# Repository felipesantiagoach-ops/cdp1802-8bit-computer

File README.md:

# CDP1802 8-bit Computer — Design and Construction

Design, construction and testing of an 8-bit microcomputer built around the **RCA CDP1802**, the first CMOS microprocessor (also known for flying in the Galileo probe and the Hubble Space Telescope).

Final engineering project for *Proyecto y Diseño Electrónico* (ET546), Electronic Engineering, **Universidad Nacional de Misiones**, Argentina (November 2022).

📄 **[Read the full report (PDF, Spanish)](informe/ProyectoFinal.pdf)**: 166 pages covering theory, schematics, PCBs, assembly code and test results.  
🖼️ **[Project poster](Poster_PyD_2022_Grupo_A.pdf)**

---

## Overview

The project was developed in three stages of increasing complexity. Each stage was designed in KiCad, simulated, and (for the first two) built and tested on hardware.

| Stage | Status | Highlights |
|---|---|---|
| **Minimal system** | ✅ Built and tested | CDP1802 + 8K EEPROM, 8-bit addressing, jumper-selectable program banks, single-sided PCB |
| **Medium system** | ✅ Built and tested | 16-bit addressing (64 KB), 32K EEPROM + 32K RAM, USB-UART link, runs Tiny BASIC and a diskless Elf/OS |
| **Final system** | 📐 Designed (schematics + PCB) | Power supply, bank-switched memory, I²C and SPI serial memories, 12-bit ADC, parallel I/O |

### 1. Minimal system
- CDP1802 with an AT28C64 EEPROM using only the 8 low address lines (256-byte programs).
- A8/A9 set by jumpers, allowing four independent programs in the same EEPROM without reprogramming.
- Four assembly programs written and verified on hardware: LED blink, push-button input, conditional blink, and a **bit-banged UART transmitter at 600 baud** using the Q output, with the delay loop derived analytically from the instruction cycle timing.
- Subroutines use the CDP1802 *SEP technique*, which requires no RAM (the system has none).

### 2. Medium system
- 74HC373 address latch to demultiplex the CDP1802's time-shared address bus to a full **16-bit / 64 KB** space.
- Memory map: 32K EEPROM (program) + 32K DS1744 timekeeping RAM (data).
- FT232RL USB-UART module for communication with a PC terminal (Tera Term).
- Ported and ran third-party software on real hardware:
  - **Tiny BASIC interpreter**: modified the source (register definitions, idle line polarity, autorun) and reassembled it.
  - **Diskless Elf/OS** operating system.

### 3. Final system (design)
Fully backwards compatible with the previous stages. Designed as a modular set of schematics and a double-sided 30 × 30 cm PCB:
- **Linear power supply** with line filter and ±12 V / 5 V regulation.
- **Bank-switched memory map**: boot mode (EEPROM + RAM) and run mode (program copied to RAM, a second RAM swapped in to maximise working memory).
- **Hardware SPI engine** built from discrete logic (MC14014 + 74HC595 shift registers, 74HC161/74HC74/74HC73 clock generator producing exactly 8 pulses at 2 MHz), which offloads the serial shifting from the CPU. Intended for a **microSD** card.
- **I²C serial memories**: 24LC1025 EEPROM and MB85RC64A **FRAM**, driven in software through the parallel port.
- **12-bit ADC** (MAX127) with OPA4277 signal conditioning for **4–20 mA** industrial current loops.
- **82C55 parallel I/O** mapped into the CDP1802's dedicated I/O space (INP/OUT instructions).

The report also outlines future work, including I/O drivers, SD-card support, a PLC-oriented use case and guidelines for a real-time operating system.

---

## Tools

| Area | Tools |
|---|---|
| Schematics and PCB | KiCad |
| Assembly and simulation | A18 cross-assembler, Emma02 emulator (debugging and instruction tracing) |
| Programming hardware | XGecu TL866 universal programmer; an Arduino-based EEPROM programmer was also built |
| Communication | FT232RL, Tera Term |
| Documentation | LaTeX (memoir, biblatex/biber), Git, VS Code |

---

## Repository structure

```
Poster_PyD_2022_Grupo_A.pdf   Project poster
informe/
  ProyectoFinal.pdf           Compiled report (Spanish)
  Codigo fuente/              LaTeX source (chapters, appendices, bibliography, figures)
archivos_de_kicad/            KiCad projects: schematics, PCBs, BOMs and exports
  1_Sistema_minimo/
  2_Sistema_medio/
  3_Sistema_final/            Full system plus separate sub-projects (ADC conditioning, SPI)
programas/                    CDP1802 assembly programs (.asm), assembled output (.hex, .lst) and build scripts
decodificador SPI/            Proteus simulations of the hardware SPI circuit
```

The KiCad projects were made with KiCad 6 (the minimal system also includes the original KiCad 5 files).  
Programs are assembled with the [A18 cross-assembler](https://www.retrotechnology.com/memship/a18.html); each folder includes a `.bat` script that assembles the `.asm` file with the same name.

### Building the report
Requires a LaTeX distribution (MiKTeX or TeX Live) with `biber`.

```bash
cd "informe/Codigo fuente"
pdflatex proyecto
biber proyecto
pdflatex proyecto
pdflatex proyecto
```

---

## Third-party software

The `programas/` folder also contains third-party code that was studied, modified or run on the hardware. It is included for reference, and credit goes to its original authors:
- **Tiny BASIC** for the 1802, from the [Membership Card](http://www.sunrise-ev.com/1802.htm) project (the `original/` folder is unmodified; `modificado/` contains our changes).
- **FIG-Forth** for the 1802, from Lee Hart's Membership Card resources.

---

## Authors

- **Felipe Santiago Alegre Chamorro**
- Atilio Boher
- Uriel Adrián Vera

Supervisor: Ing. Ricardo A. Korpys, Facultad de Ingeniería, UNaM.

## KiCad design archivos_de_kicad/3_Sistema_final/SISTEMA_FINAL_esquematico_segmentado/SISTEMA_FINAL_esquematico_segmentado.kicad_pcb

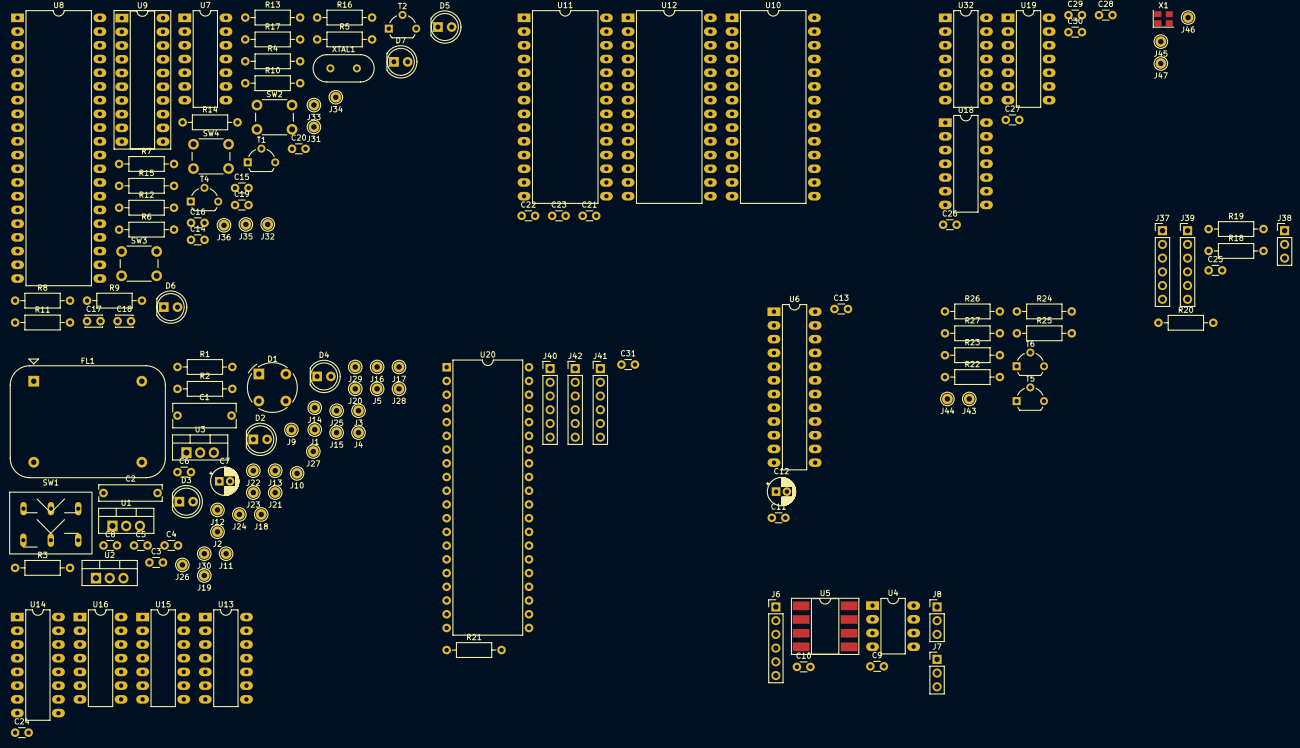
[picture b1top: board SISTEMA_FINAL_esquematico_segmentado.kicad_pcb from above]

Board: 2 copper layers, 144 parts (0 on the bottom side), 133 nets, no tracks yet.

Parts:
C1: 4700 uf; C_Rect_L11.5mm_W4.3mm_P10.00mm_MKT
C2: 4700 uf; C_Rect_L11.5mm_W2.8mm_P10.00mm_MKT
C3, C4: 0.33; C_Disc_D3.0mm_W1.6mm_P2.50mm
C5, C8: 0.1uf; C_Disc_D3.0mm_W1.6mm_P2.50mm
C6: 0.1 uf; C_Disc_D3.0mm_W1.6mm_P2.50mm
C7: 10 uf; CP_Radial_D5.0mm_P2.00mm
C9, C10, C13, C19, C21, C24, C25, C26, C27, C28, C29, C30, C31: 0.1uF; C_Disc_D3.0mm_W1.6mm_P2.50mm
C11: 0.01 uf; C_Disc_D3.0mm_W1.6mm_P2.50mm
C12: 4.7 uf; CP_Radial_D5.0mm_P2.00mm
C14, C15, C16, C20, C22, C23: 0,1uF; C_Disc_D3.0mm_W1.6mm_P2.50mm
C17, C18: 30pF; C_Disc_D3.0mm_W2.0mm_P2.50mm
D1: B380R; Diode_Bridge_Round_D9.0mm
D2, D3, D4, D5, D6, D7: LD271; LED_D5.0mm
FL1: 1FP41-4R; Filter_FILTERCON_1FPxx
J1, J2, J3, J4, J5, J9, J10, J11, J12, J13, J14, J15, J16, J17, J18, J19, J20, J21, J22, J23, J24, J25, J26, J27, J28, J29, J30, J32, J34, J36, J43, J44, J45, J46, J47: 1; Pin_D1.0mm_L10.0mm
J6, J37, J39, J40, J41, J42: Conn_01x06_Male; PinHeader_1x06_P2.54mm_Vertical
J7, J8, J38: N1,2,3; PinHeader_1x03_P2.54mm_Vertical
J31: 3; Pin_D1.0mm_L10.0mm
J33, J35: 4; Pin_D1.0mm_L10.0mm
R1, R2: 1 k; R_Axial_DIN0207_L6.3mm_D2.5mm_P10.16mm_Horizontal
R3: 330; R_Axial_DIN0207_L6.3mm_D2.5mm_P10.16mm_Horizontal
R4, R5, R6: 100k; R_Axial_DIN0207_L6.3mm_D2.5mm_P10.16mm_Horizontal
R7: 10M; R_Axial_DIN0207_L6.3mm_D2.5mm_P10.16mm_Horizontal
R8, R9, R10, R18, R21: 47K; R_Axial_DIN0207_L6.3mm_D2.5mm_P10.16mm_Horizontal
R11, R19, R20: 47k; R_Axial_DIN0207_L6.3mm_D2.5mm_P10.16mm_Horizontal
R12, R14, R16, R22, R23, R26, R27: 10K; R_Axial_DIN0207_L6.3mm_D2.5mm_P10.16mm_Horizontal
R13, R15, R17: 220; R_Axial_DIN0207_L6.3mm_D2.5mm_P10.16mm_Horizontal
R24, R25: 100K; R_Axial_DIN0207_L6.3mm_D2.5mm_P10.16mm_Horizontal
SW1: SW_Push_DPDT; llave_6pin
SW2, SW3, SW4: SW_Push; SW_PUSH_6mm_H4.3mm
T1, T2, T4, T5, T6: PN2222A; TO-92L_Wide
U1: L7812; TO-220-3_Vertical
U2: L7912; TO-220-3_Vertical
U3: L7805; TO-220-3_Vertical
U4: 24LC1025; DIP-8_W7.62mm_LongPads
U5: MB85RC64; DIP-8_W8.89mm_SMDSocket_LongPads
U6: MAX127; DIP-24_W7.62mm_LongPads
U7, U19, U32: 74HC132; DIP-14_W7.62mm_LongPads
U8: CDP1802ACE; DIP-40_W15.24mm_LongPads
U9: 74HC73; DIP-20_W7.62mm_Socket_LongPads
U10: EEPROM; DIP-28_W15.24mm_LongPads
U11: NV_RAM1; DIP-28_W15.24mm_LongPads
U12: NV_RAM2; DIP-28_W15.24mm_LongPads
U13, U15, U16, U18: 74HC00; DIP-14_W7.62mm_LongPads
U14: 74HC138; DIP-16_W7.62mm_LongPads
U20: 82C55A; DIP-40_W15.24mm
X1: XO-25-4MHz; Oscillator_SMD_Abracon_ASE-4Pin_3.2x2.5mm
XTAL1: 4 MHz; Crystal_HC18-U_Vertical

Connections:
/Decodificador/A15: U13.2, U13.5
/Mapa_de_memoria/A0: U10.10 (A0), U11.10 (A0), U12.10 (A0)
/Mapa_de_memoria/A1: U10.9 (A1), U11.9 (A1), U12.9 (A1)
/Mapa_de_memoria/A2: U10.8 (A2), U11.8 (A2), U12.8 (A2)
/Mapa_de_memoria/A3: U10.7 (A3), U11.7 (A3), U12.7 (A3)
/Mapa_de_memoria/A4: U10.6 (A4), U11.6 (A4), U12.6 (A4)
/Mapa_de_memoria/A5: U10.5 (A5), U11.5 (A5), U12.5 (A5)
/Mapa_de_memoria/A6: U10.4 (A6), U11.4 (A6), U12.4 (A6)
/Mapa_de_memoria/A7: U10.3 (A7), U11.3 (A7), U12.3 (A7)
/Mapa_de_memoria/A8: U10.25 (A8), U11.25 (A8), U12.25 (A8)
/Mapa_de_memoria/A9: U10.24 (A9), U11.24 (A9), U12.24 (A9)
/Mapa_de_memoria/A10: U10.21 (A10), U11.21 (A10), U12.21 (A10)
/Mapa_de_memoria/A11: U10.23 (A11), U11.23 (A11), U12.23 (A11)
/Mapa_de_memoria/A12: U10.2 (A12), U11.2 (A12), U12.2 (A12)
/Mapa_de_memoria/A13: U10.26 (A13), U11.26 (A13), U12.26 (A13)
/Mapa_de_memoria/A14: U10.1 (A14), U11.1 (A14), U12.1 (A14)
/Mapa_de_memoria/D0: U10.11 (Q0), U11.11 (Q0), U12.11 (Q0)
/Mapa_de_memoria/D1: U10.12 (Q1), U11.12 (Q1), U12.12 (Q1)
/Mapa_de_memoria/D2: U10.13 (Q2), U11.13 (Q2), U12.13 (Q2)
/Mapa_de_memoria/D3: U10.15 (Q3), U11.15 (Q3), U12.15 (Q3)
/Mapa_de_memoria/D4: U10.16 (Q4), U11.16 (Q4), U12.16 (Q4)
/Mapa_de_memoria/D5: U10.17 (Q5), U11.17 (Q5), U12.17 (Q5)
/Mapa_de_memoria/D6: U10.18 (Q6), U11.18 (Q6), U12.18 (Q6)
/Mapa_de_memoria/D7: U10.19 (Q7), U11.19 (Q7), U12.19 (Q7)
/Microprocesador/A0: U8.25 (MA0), U9.3 (D0)
/Microprocesador/A1: U8.26 (MA1), U9.4 (D1)
/Microprocesador/A2: U8.27 (MA2), U9.7 (D2)
/Microprocesador/A3: U8.28 (MA3), U9.8 (D3)
/Microprocesador/A4: U8.29 (MA4), U9.13 (D4)
/Microprocesador/A5: U8.30 (MA5), U9.14 (D5)
/Microprocesador/A6: U8.31 (MA6), U9.17 (D6)
/Microprocesador/A7: U8.32 (MA7), U9.18 (D7)
CS_EEPROM: U10.20 (~CS), U15.11
CS_RAM1: U11.20 (~CS), U13.6
CS_RAM2: U12.20 (~CS), U16.11
CS_SPI: U13.4, U14.9 (O6)
EF3: J39.5, U8.22 (~EF3)
EF4: J39.2, U8.21 (~EF4)
EFx: J37.3, J39.3, J39.4, R18.1
Earth: C1.2, C2.1, C3.2, C4.1, C5.2, C6.1, C7.2, C8.2, C9.1, C10.1, C11.2, C12.2, C13.2, C17.2, C18.2, C19.2, C20.2, C21.2, C22.2, C23.2, C24.2, C25.2, C26.2, C27.2, C28.2, C29.2, C30.2, C31.2, D2.1 (K), D4.1 (K), J3.1, J6.1, J7.1, J8.1, J13.1, J14.1, J16.1, J17.1, J18.1, J19.1, J21.1, J22.1, J23.1, J24.1, J25.1, J26.1, J27.1, J28.1, J29.1, J30.1, J37.6, R2.1, R4.1, R5.1, R6.1, R21.1, R24.1, R25.1, T1.1 (E), T2.1 (E), T4.1 (E), T5.1 (E), T6.1 (E), U1.2 (GND), U2.1 (GND), U3.2 (GND), U4.4 (GND), U5.1 (A0), U5.2 (A1), U5.3 (A2), U5.4 (GND), U6.4 (DGND), U6.6 (A0), U6.8 (A2), U6.10 (A1), U6.12 (AGND), U8.20 (VSS), U9.1 (OE), U9.10 (GND), U10.14 (GND), U11.14 (GND), U12.14 (GND), U13.7 (GND), U14.8 (GND), U15.7 (GND), U16.7 (GND), U18.7 (GND), U19.7 (GND), U20.7 (GND), U32.12, U32.13, X1.2 (GND)
MOSI: J6.4, J45.1, J46.1
MRD: J33.1, U8.7 (~MRD), U10.22 (~OE), U11.22 (~OE), U12.22 (~OE), U16.1
MWR: J35.1, U8.35 (~MWR), U10.27 (~WE), U11.27 (~WE), U12.27 (~WE)
N0: U8.19 (N0), U20.9 (A0)
N1: U8.18 (N1), U20.8 (A1)
N2: U8.17 (N2), U18.10
unnamed: C1.1, C3.1, D1.1 (+), U1.1 (IN)
unnamed: C2.2, C4.2, D1.3 (-), U2.2 (VI)
unnamed: C11.1, U6.23 (REFADJ)
unnamed: C12.1, U6.21 (REF)
unnamed: C14.2, R4.2, SW2.1, U7.1, U7.2
unnamed: C15.2, R5.2, SW3.1, U7.4, U7.5
unnamed: C16.2, R6.2, SW4.1, U7.9, U7.10
unnamed: C17.1, R7.1, U8.1 (CLOCK), XTAL1.1
unnamed: C18.1, R7.2, U8.39 (~XTAL), XTAL1.2
unnamed: D2.2 (A), R1.2
unnamed: D3.2 (A), R2.2
unnamed: D4.2 (A), R3.2
unnamed: D5.1 (K), T1.3 (C)
unnamed: D5.2 (A), R13.2
unnamed: D6.1 (K), T2.3 (C)
unnamed: D6.2 (A), R15.2
unnamed: D7.1 (K), T4.3 (C)
unnamed: D7.2 (A), R17.2
unnamed: FL1.1, J1.1
unnamed: FL1.2 (P'), SW1.2 (B)
unnamed: FL1.3 (N), J2.1
unnamed: FL1.4 (N'), SW1.5 (B)
unnamed: J37.1, J38.3
unnamed: J37.5, J38.1
unnamed: J39.1, R20.2
unnamed: J39.6, R19.2
unnamed: J40.1, U20.37 (PA7)
unnamed: J40.2, U20.38 (PA6)
unnamed: J40.3, U20.39 (PA5)
unnamed: J40.4, U20.40 (PA4)
unnamed: J40.5, U20.1 (PA3)
unnamed: J40.6, U20.2 (PA2)
unnamed: J41.1, U20.25 (PB7)
unnamed: J41.2, U20.24 (PB6)
unnamed: J41.3, U20.23 (PB5)
unnamed: J41.4, U20.22 (PB4)
unnamed: J41.5, U20.21 (PB3)
unnamed: J41.6, U20.20 (PB2)
unnamed: J42.1, U20.11 (PC6)
unnamed: J42.2, U20.12 (PC5)
unnamed: J42.3, U20.13 (PC4)
unnamed: J42.4, U20.17 (PC3)
unnamed: J42.5, U20.16 (PC2)
unnamed: J42.6, U20.15 (PC1)
unnamed: R8.2, U8.38 (~DMA_IN)
unnamed: R9.2, U8.37 (~DMA_OUT)
unnamed: R10.2, U8.36 (~INTERRUPT)
unnamed: R11.2, U8.2 (~WAIT)
unnamed: R12.1, U8.6 (SC0)
unnamed: R12.2, T1.2 (B)
unnamed: R14.1, U8.5 (SC1)
unnamed: R14.2, T2.2 (B)
unnamed: R16.1, U8.4 (Q)
unnamed: R16.2, T4.2 (B)
unnamed: R22.2, R24.2, T5.2 (B)
unnamed: R23.2, R25.2, T6.2 (B)
unnamed: U6.17 (CH4), U6.18 (CH5), U6.19 (CH6), U6.20 (CH7)
unnamed: U7.3, U8.3 (~CLEAR)
unnamed: U7.6, U8.24 (~EF1)
unnamed: U7.8, U8.23 (~EF2)
unnamed: U13.3, U14.4 (E1), U15.12, U16.13
unnamed: U13.8, U15.13
unnamed: U13.11, U14.5 (E2)
unnamed: U15.3, U16.4, U18.1
unnamed: U15.6, U20.35 (RESET)
unnamed: U15.8, U18.5, U18.13
unnamed: U16.3, U16.9, U20.5 (~RD)
unnamed: U16.5, U18.11
unnamed: U16.6, U18.2, U18.12
unnamed: U16.8, U20.36 (~WR)
unnamed: U18.3, U18.4
unnamed: U18.6, U18.9
unnamed: U18.8, U20.6 (~CS)
PA0: J43.1, R27.1, T6.3 (C), U4.5 (SDA), U5.5 (SDA), U6.7 (SDA), U20.4 (PA0)
PA1: J44.1, R26.1, T5.3 (C), U4.6 (SCL), U5.6 (SCL), U6.5 (SCL), U20.3 (PA1)
PB0: R23.1, U20.18 (PB0)
PB1: R22.1, U20.19 (PB1)
PC0: R21.2, U13.9, U16.12, U20.14 (PC0)
Q: J31.1, J37.2
SCK: J6.5, J47.1
TPA: J32.1, U8.34 (TPA), U9.11 (LE), U15.1
TPB: J34.1, U8.33 (TPB), U15.9, U16.10
VCC: C8.1, C9.2, C10.2, C13.1, C14.1, C15.1, C16.1, C19.1, C20.1, C21.1, C22.1, C23.1, C24.1, C25.1, C26.1, C27.1, C28.1, C29.1, C30.1, C31.1, J4.1, J5.1, J6.2, J7.3, J8.3, J9.1, J10.1, J11.1, J12.1, J37.4, J38.2, R3.1, R8.1, R9.1, R10.1, R11.1, R13.1, R15.1, R17.1, R18.2, R19.1, R20.1, R26.2, R27.2, SW2.2, SW3.2, SW4.2, U3.3 (OUT), U4.1 (A0), U4.2 (A1), U4.3 (A2), U4.8 (VCC), U5.8 (VCC), U6.1 (VDD), U6.2 (VDD), U6.11 (SHDN), U8.16 (VCC), U8.40 (VDD), U9.20 (VCC), U10.28 (VCC), U11.28 (VCC), U12.28 (VCC), U13.1, U13.10, U13.13, U13.14 (VCC), U14.16 (VCC), U15.2, U15.5, U15.10, U15.14 (VCC), U16.2, U16.14 (VCC), U18.14 (VCC), U19.14 (VCC), U20.26 (VCC), X1.1 (EN), X1.4 (Vdd)
VCC_12V: C5.1, C7.1, J15.1, R1.1, U1.3 (OUT), U3.1 (IN)
VCC_-12V: C6.2, D3.1 (K), J20.1, U2.3 (VO)
WP1: J7.2, U4.7 (WP)
WP2: J8.2, U5.7 (WP)
